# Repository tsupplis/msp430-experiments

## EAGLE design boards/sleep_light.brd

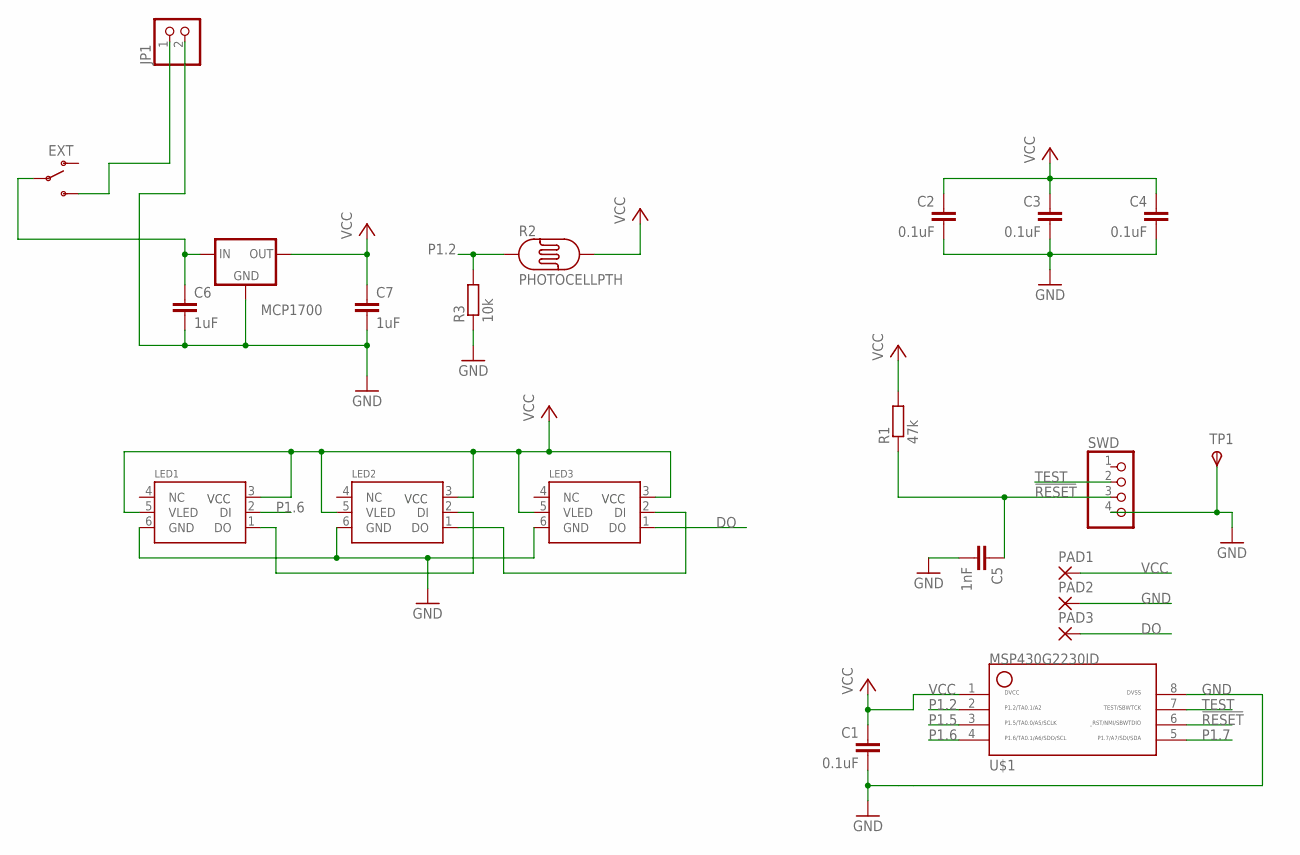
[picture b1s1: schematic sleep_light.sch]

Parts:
C1, C2, C3, C4: 0.1uF; C0805
C5: 1nF; C0805
C6, C7: 1uF; C0805
JP1: PINHD-1X2; 1X02
LED1, LED2, LED3: 5050WS2811W; RGBLED5050W
MCP1700: MCP1700; SOT-23
ON: EXT; SWITCH-SPDT
PAD1, PAD2, PAD3: SMD2; SMD1,27-2,54
R1: 47k; R0805
R2: PHOTOCELLPTH; PHOTOCELL
R3: 10k; R0805
SWD: PINHD-1X4; 1X04
TP1: TPSTP20R; TP20R
U$1: MSP430G2230ID; SO08

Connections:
!RESET: C5.1, R1.1, SWD.3, U$1.6
DO: LED3.1 (DO), PAD3.1
GND: C1.2, C2.2, C3.2, C4.2, C5.2, C6.2, C7.2, JP1.2, LED1.6 (GND), LED2.6 (GND), LED3.6 (GND), MCP1700.1 (GND), PAD2.1, R3.1, SWD.4, TP1.TP, U$1.8
unnamed: JP1.1, ON.3 (S)
unnamed: LED2.1 (DO), LED3.2 (DI)
unnamed: LED1.1 (DO), LED2.2 (DI)
unnamed: C6.1, MCP1700.3 (IN), ON.2
P1.2: R2.1, R3.2, U$1.2
P1.5: U$1.3
P1.6: LED1.2 (DI), U$1.4
P1.7: U$1.5
TEST: SWD.2, U$1.7
VCC: C1.1, C2.1, C3.1, C4.1, C7.1, LED1.3 (VCC), LED1.5 (VLED), LED2.3 (VCC), LED2.5 (VLED), LED3.3 (VCC), LED3.5 (VLED), MCP1700.2 (OUT), PAD1.1, R1.2, R2.2, U$1.1

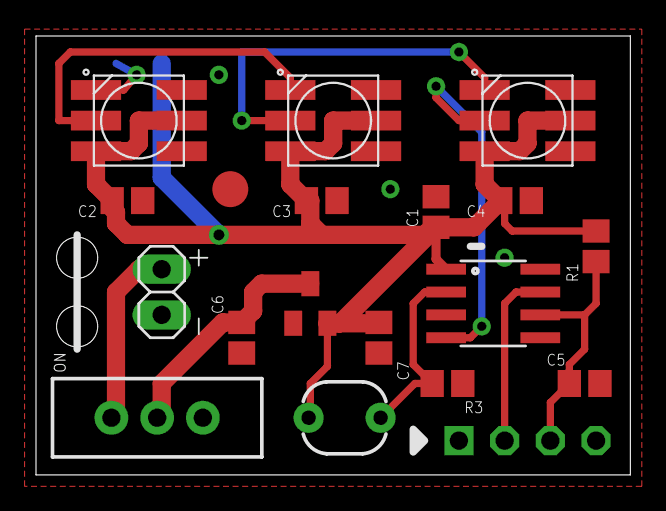
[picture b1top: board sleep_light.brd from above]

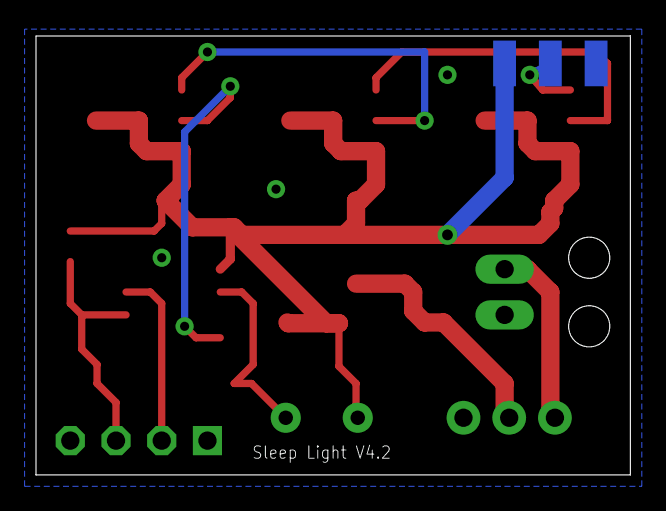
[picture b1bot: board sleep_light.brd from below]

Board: 2 copper layers, 33.0 x 24.4 mm, 22 parts (3 on the bottom side), 11 nets.

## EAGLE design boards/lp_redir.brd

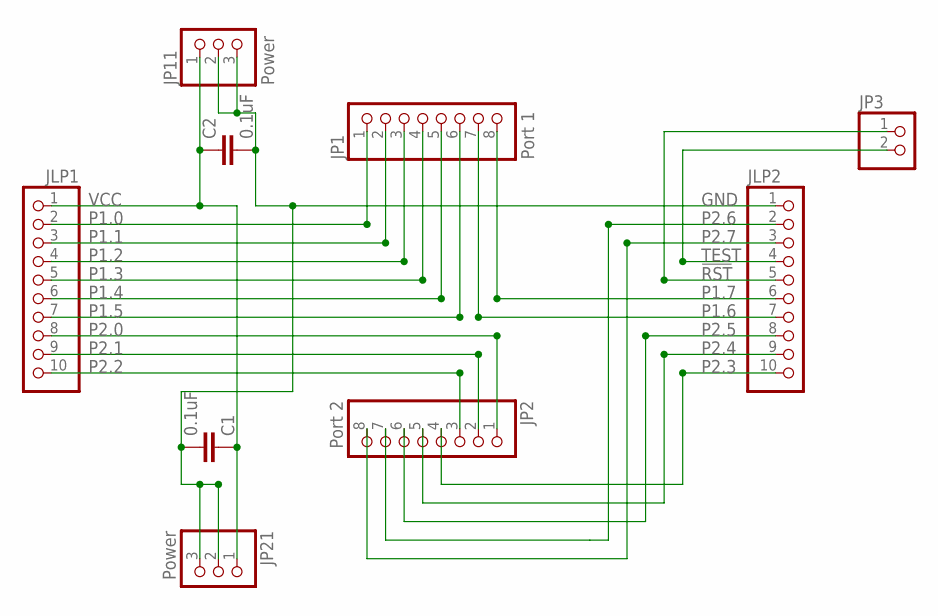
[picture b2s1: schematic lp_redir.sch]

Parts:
C1, C2: 0.1uF; C025-025X050
JLP1, JLP2: PH1X10OCT076; PH1X10OCT76
JP1: Port 1; 1X08
JP2: Port 2; 1X08
JP3: 1X02
JP11, JP21: Power; 1X03

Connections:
!RST: JLP2.5, JP3.1
GND: C1.2, C2.2, JLP2.1, JP11.2, JP11.3, JP21.2, JP21.3
P1.0: JLP1.2, JP1.1
P1.1: JLP1.3, JP1.2
P1.2: JLP1.4, JP1.3
P1.3: JLP1.5, JP1.4
P1.4: JLP1.6, JP1.5
P1.5: JLP1.7, JP1.6
P1.6: JLP2.7, JP1.7
P1.7: JLP2.6, JP1.8
P2.0: JLP1.8, JP2.1
P2.1: JLP1.9, JP2.2
P2.2: JLP1.10, JP2.3
P2.3: JLP2.10, JP2.4
P2.4: JLP2.9, JP2.5
P2.5: JLP2.8, JP2.6
P2.6: JLP2.2, JP2.7
P2.7: JLP2.3, JP2.8
TEST: JLP2.4, JP3.2
VCC: C1.1, C2.1, JLP1.1, JP11.1, JP21.1

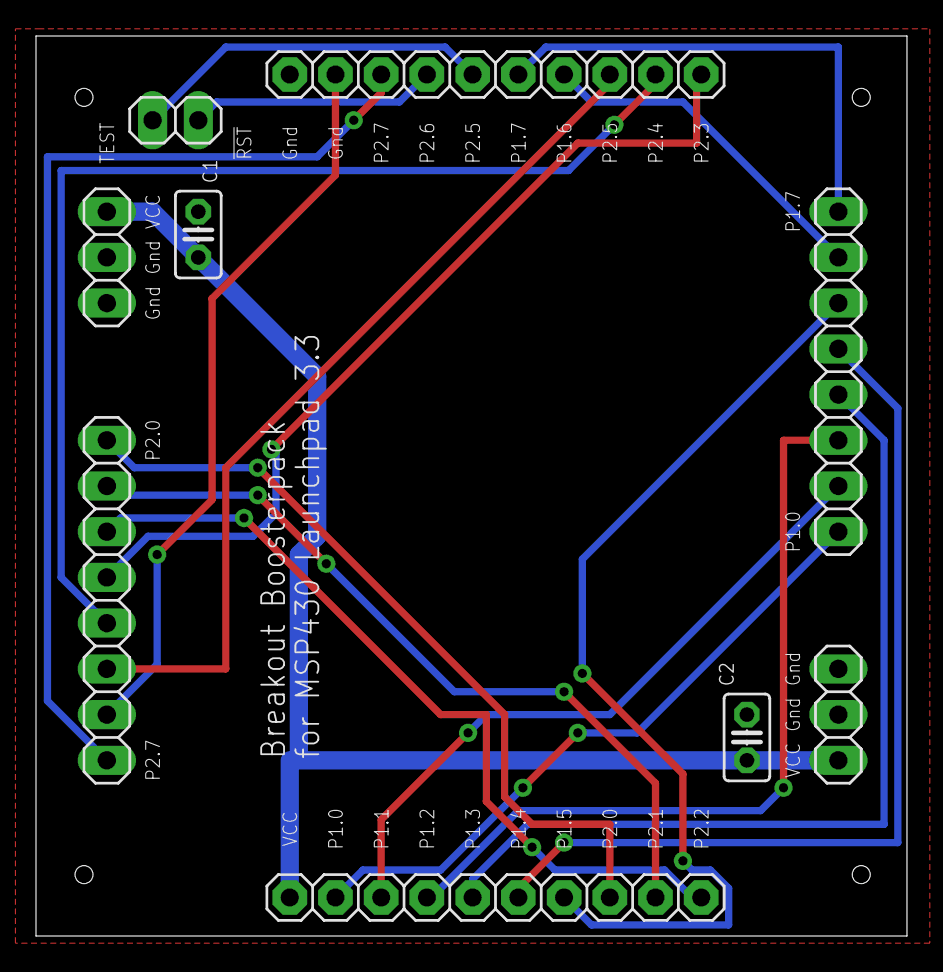
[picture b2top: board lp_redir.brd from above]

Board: 2 copper layers, 48.4 x 50.0 mm, 9 parts (0 on the bottom side), 20 nets.

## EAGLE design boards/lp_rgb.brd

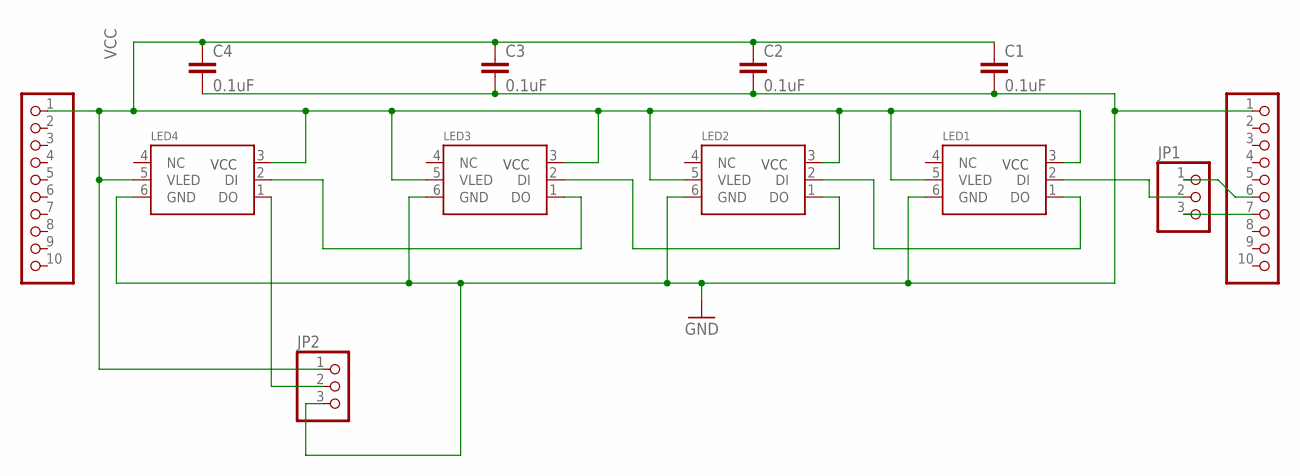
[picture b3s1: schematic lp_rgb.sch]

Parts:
C1, C2, C3, C4: 0.1uF; C0805
J1: J1; 1X10
J2: J2; 1X10
JP1, JP2: PINHD-1X3; 1X03
LED1, LED2, LED3, LED4: 5050WS2811W; RGBLED5050W

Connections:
GND: C1.2, C2.2, C3.2, C4.2, J2.1, JP2.3, LED1.6 (GND), LED2.6 (GND), LED3.6 (GND), LED4.6 (GND)
unnamed: J2.6, JP1.1
unnamed: JP2.2, LED4.1 (DO)
unnamed: LED1.1 (DO), LED2.2 (DI)
unnamed: LED2.1 (DO), LED3.2 (DI)
unnamed: LED3.1 (DO), LED4.2 (DI)
unnamed: J2.7, JP1.3
P1.6: JP1.2, LED1.2 (DI)
VCC: C1.1, C2.1, C3.1, C4.1, J1.1, JP2.1, LED1.3 (VCC), LED1.5 (VLED), LED2.3 (VCC), LED2.5 (VLED), LED3.3 (VCC), LED3.5 (VLED), LED4.3 (VCC), LED4.5 (VLED)

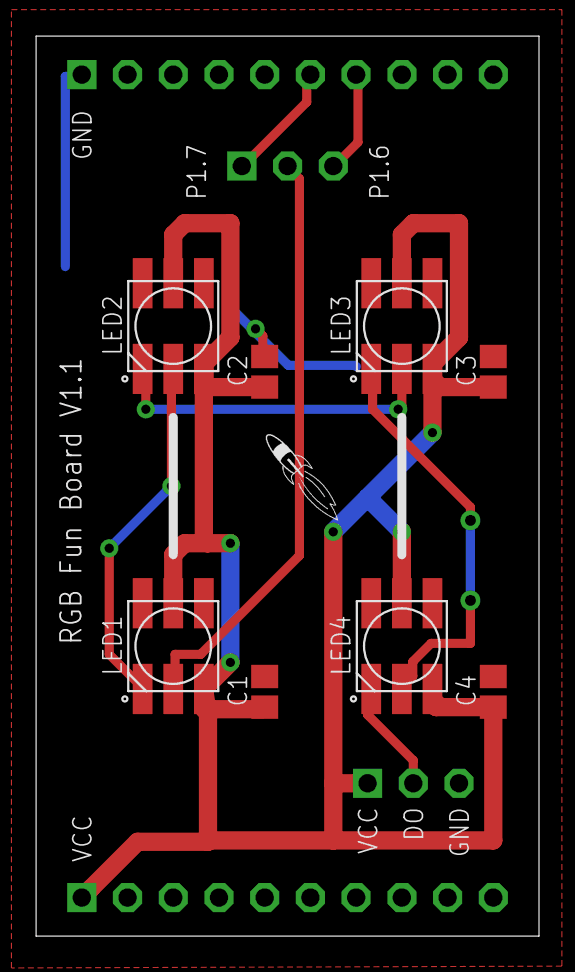
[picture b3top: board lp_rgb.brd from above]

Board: 2 copper layers, 27.9 x 50.0 mm, 13 parts (0 on the bottom side), 9 nets.

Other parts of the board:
U$2: LOGO-ROCKET

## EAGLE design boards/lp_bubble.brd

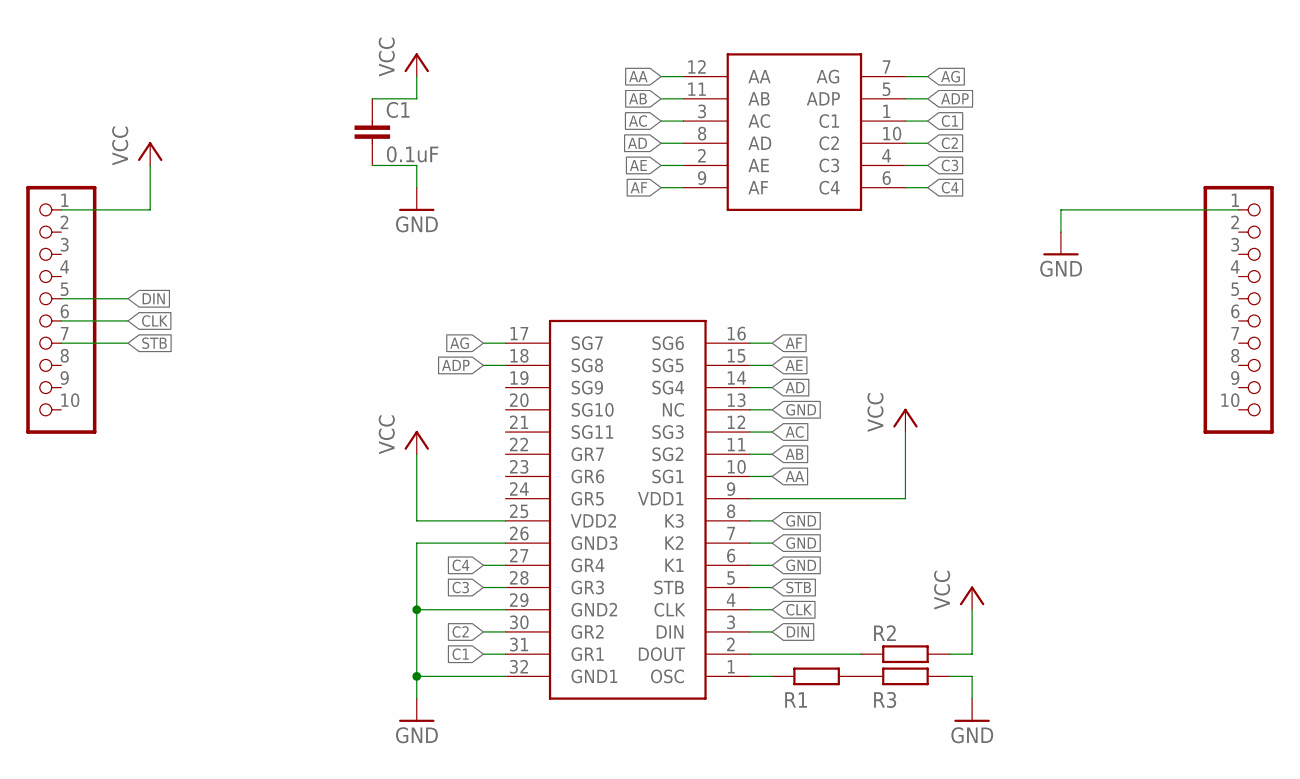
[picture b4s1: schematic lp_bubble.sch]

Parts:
C1: 0.1uF; C0805
J1: J1; 1X10
J2: J2; 1X10
R1: 50K; M0805
R2: 10K; M0805
R3: 1K; M0805
U$1: HP5082-7414
U$3: PT6961

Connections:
AA: U$1.12 (AA), U$3.10 (SG1)
AB: U$1.11 (AB), U$3.11 (SG2)
AC: U$1.3 (AC), U$3.12 (SG3)
AD: U$1.8 (AD), U$3.14 (SG4)
ADP: U$1.5 (ADP), U$3.18 (SG8)
AE: U$1.2 (AE), U$3.15 (SG5)
AF: U$1.9 (AF), U$3.16 (SG6)
AG: U$1.7 (AG), U$3.17 (SG7)
C1: U$1.1 (C1), U$3.31 (GR1)
C2: U$1.10 (C2), U$3.30 (GR2)
C3: U$1.4 (C3), U$3.28 (GR3)
C4: U$1.6 (C4), U$3.27 (GR4)
CLK: J1.6, U$3.4 (CLK)
DIN: J1.5, U$3.3 (DIN)
GND: C1.2, J2.1, R3.2, U$3.6 (K1), U$3.7 (K2), U$3.8 (K3), U$3.13 (NC), U$3.26 (GND3), U$3.29 (GND2), U$3.32 (GND1)
unnamed: R1.2, R3.1
unnamed: R1.1, U$3.1 (OSC)
unnamed: R2.1, U$3.2 (DOUT)
STB: J1.7, U$3.5 (STB)
VCC: C1.1, J1.1, R2.2, U$3.9 (VDD1), U$3.25 (VDD2)

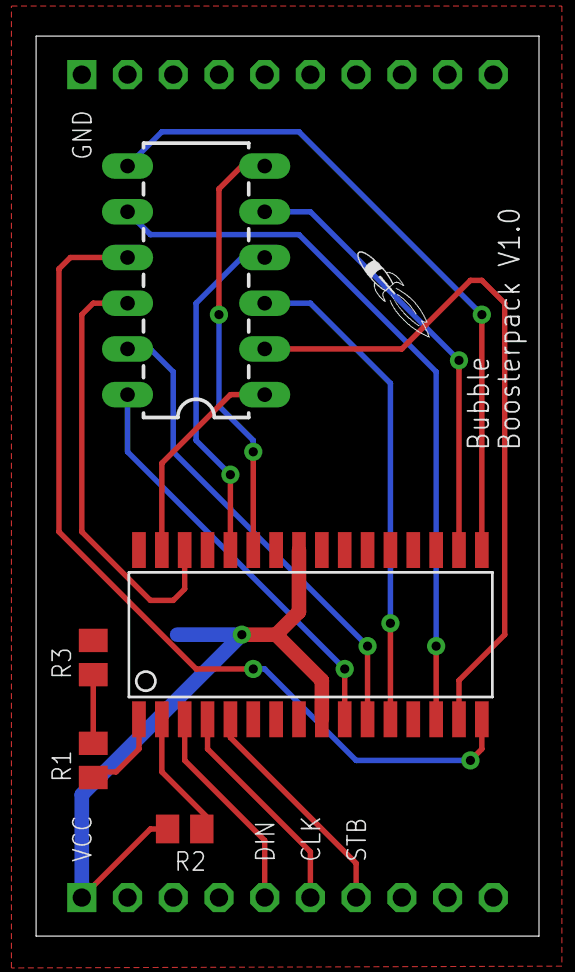
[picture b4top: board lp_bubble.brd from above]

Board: 2 copper layers, 27.9 x 50.0 mm, 9 parts (1 on the bottom side), 20 nets.

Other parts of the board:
U$2: LOGO-ROCKET

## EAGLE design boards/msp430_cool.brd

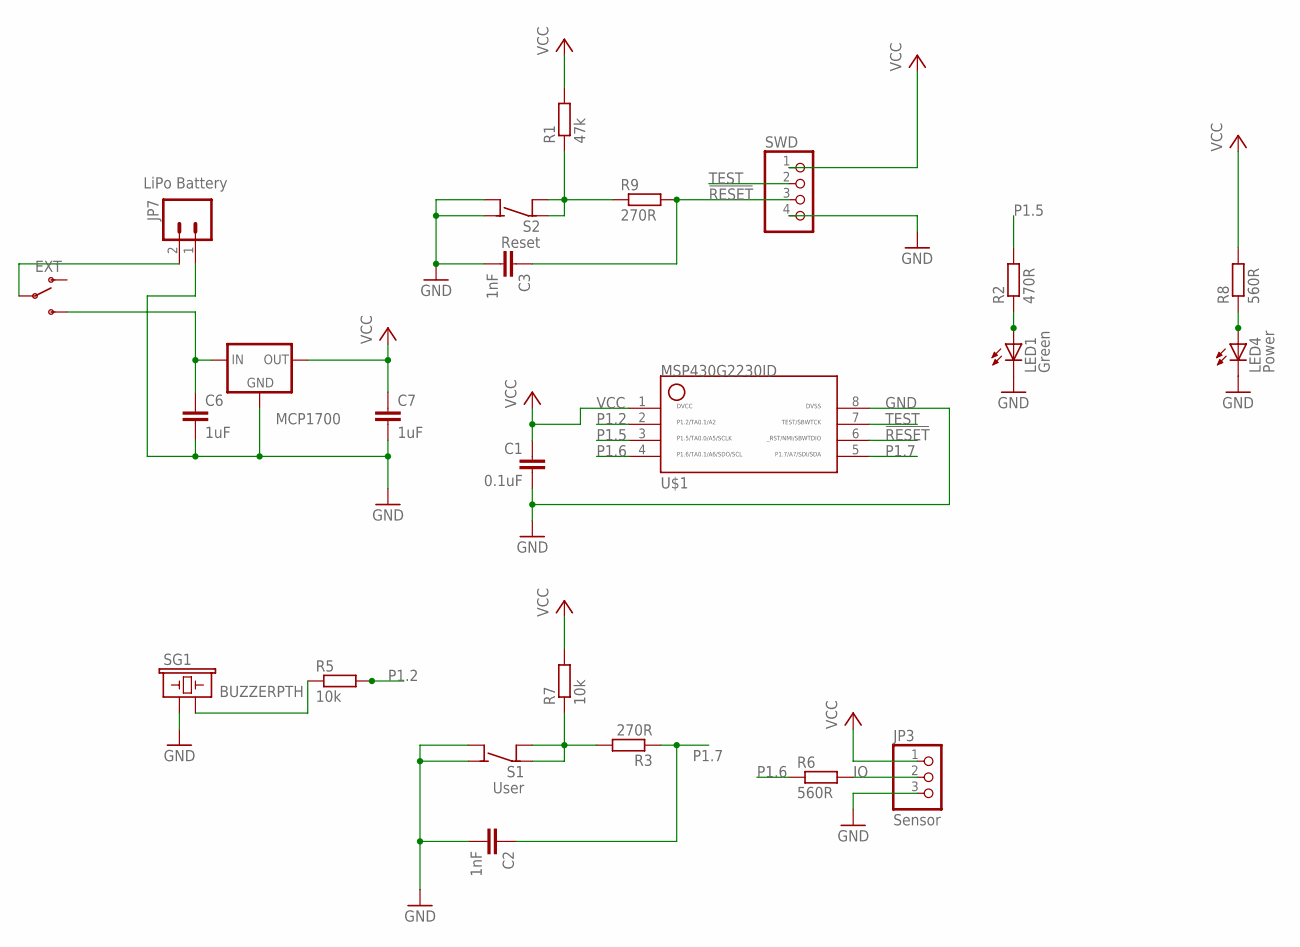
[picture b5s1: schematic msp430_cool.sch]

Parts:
C1: 0.1uF; C0805
C2, C3: 1nF; C0805
C6, C7: 1uF; C0805
JP3: Sensor; 1X03
JP7: LiPo Battery; JST-2-PTH
LED1: Green; CHIPLED_1206
LED4: Power; CHIPLED_1206
MCP1700: MCP1700; SOT-23
ON: EXT; SWITCH-SPDT
R1: 47k; R0805
R2: 470R; R0805
R3, R9: 270R; R0805
R5, R7: 10k; R0805
R6, R8: 560R; R0805
S1: User; 6MMTACTILE_4PIN
S2: Reset; 6MMTACTILE_4PIN
SG1: BUZZERPTH; BUZZER-12MM
SWD: PINHD-1X4; 1X04
U$1: MSP430G2230ID; SO08

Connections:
!RESET: C3.1, R9.2, SWD.3, U$1.6
GND: C1.2, C2.2, C3.2, C6.2, C7.2, JP3.3, JP7.1, LED1.C, LED4.C, MCP1700.1 (GND), S1.A1 (NO), S1.A2 (NO), S2.A1 (NO), S2.A2 (NO), SG1.+ (1), SWD.4, U$1.8
IO: JP3.2, R6.2
unnamed: LED4.A, R8.1
unnamed: JP7.2, ON.2
unnamed: LED1.A, R2.1
unnamed: R1.1, R9.1, S2.B1 (COM), S2.B2 (COM)
unnamed: R5.1, SG1.- (2)
unnamed: R3.2, R7.1, S1.B1 (COM), S1.B2 (COM)
unnamed: C6.1, MCP1700.3 (IN), ON.3 (S)
P1.2: R5.2, U$1.2
P1.5: R2.2, U$1.3
P1.6: R6.1, U$1.4
P1.7: C2.1, R3.1, U$1.5
TEST: SWD.2, U$1.7
VCC: C1.1, C7.1, JP3.1, MCP1700.2 (OUT), R1.2, R7.2, R8.2, SWD.1, U$1.1

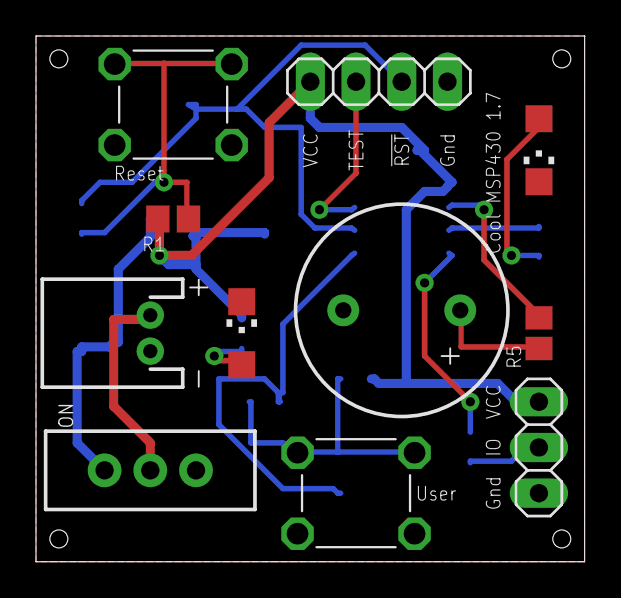
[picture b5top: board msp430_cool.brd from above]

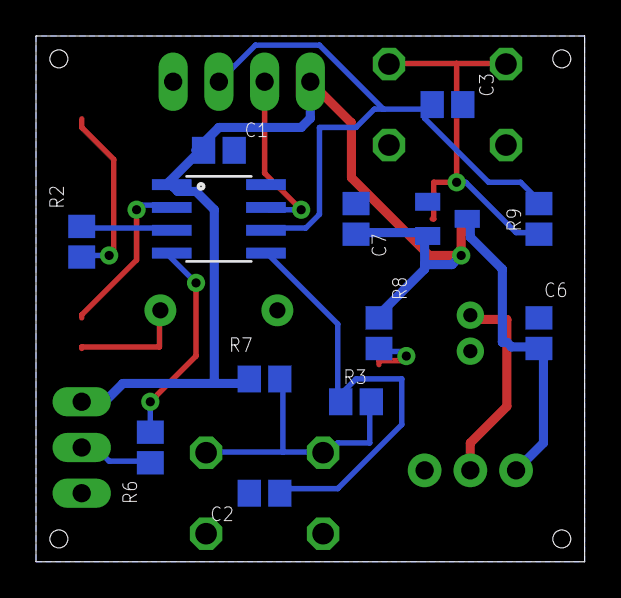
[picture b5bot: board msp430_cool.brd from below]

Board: 2 copper layers, 30.5 x 29.2 mm, 24 parts (13 on the bottom side), 16 nets.

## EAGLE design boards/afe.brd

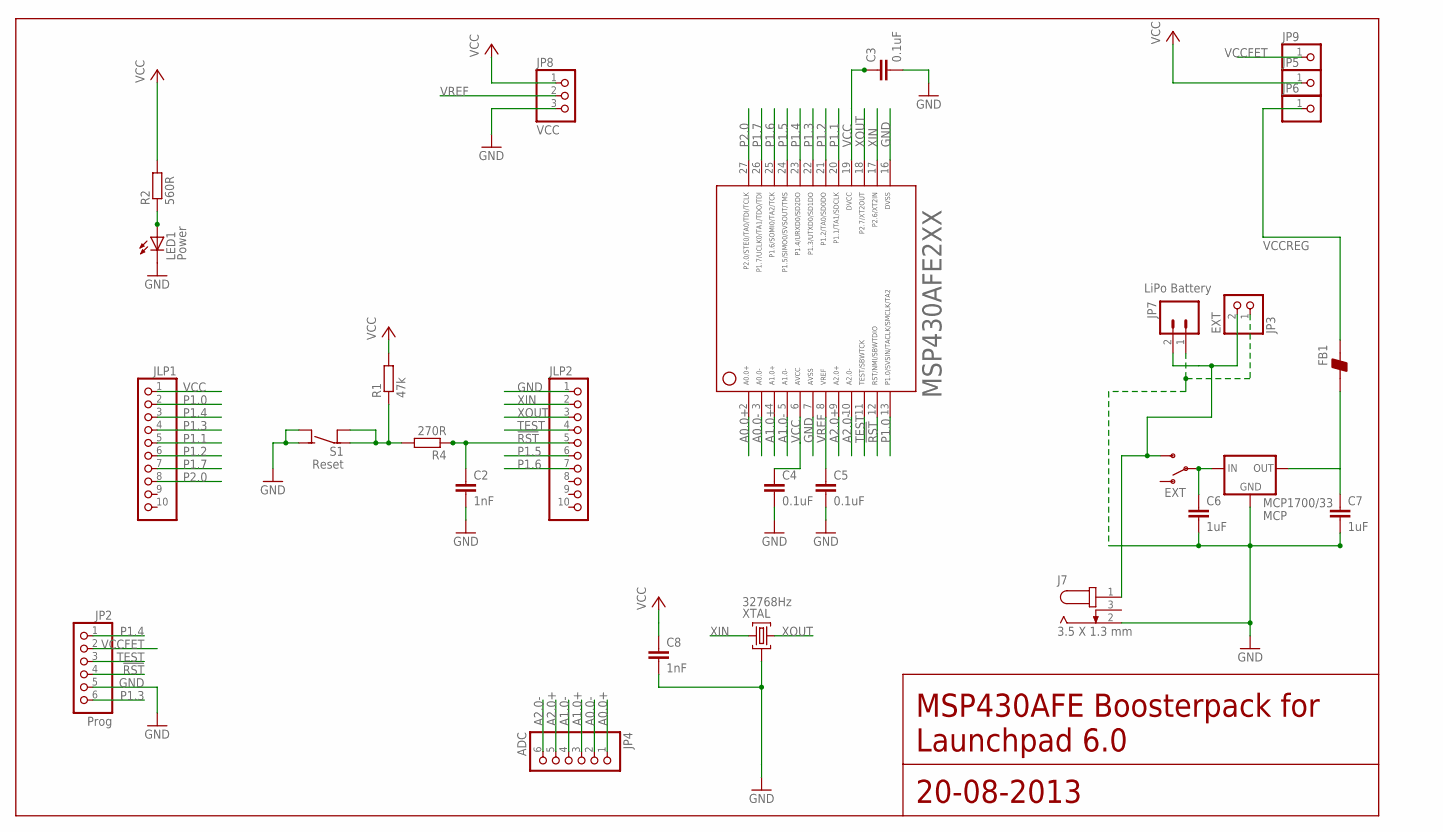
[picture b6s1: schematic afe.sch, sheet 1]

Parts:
C2, C8: 1nF; C0805
C3, C4, C5: 0.1uF; C0805
C6, C7: 1uF; C0805
FB1: BEAD-0805; 0805
J7: 3.5 X 1.3 mm; 3.5X1.3MM_DC_JACK
JLP1, JLP2: PH1X10OCT076; PH1X10OCT76
JP2: Prog; 1X06
JP3: EXT; 1X02
JP4: ADC; 1X06
JP5, JP6, JP9: PINHD-1X1; 1X01
JP7: LiPo Battery; JST-2-PTH
JP8: VCC; 1X03
LED1: Power; CHIPLED_1206
MCP1700/33: MCP; SOT-23
MSP430AFE: AFE2XX--PW24; PW24
ON: EXT; SWITCH-SPDT
R1: 47k; R0805
R2: 560R; R0805
R4: 270R; R0805
S1: Reset; 6MMTACTILE_4PIN
XTAL: 32768Hz; QUARZ5

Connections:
!RST: C2.1, JLP2.5, JP2.4, MSP430AFE.12 (11), R4.1
A0.0+: JP4.1, MSP430AFE.2 (1)
A0.0-: JP4.2, MSP430AFE.3 (2)
A1.0+: JP4.3, MSP430AFE.4 (3)
A1.0-: JP4.4, MSP430AFE.5 (4)
A2.0+: JP4.5, MSP430AFE.9 (8)
A2.0-: JP4.6, MSP430AFE.10 (9)
GND: C2.2, C3.2, C4.2, C5.2, C6.2, C7.2, C8.2, J7.2, JLP2.1, JP2.5, JP3.1, JP7.1, JP8.3, LED1.C, MCP1700/33.1 (GND), MSP430AFE.7 (6), MSP430AFE.16 (13), S1.A1 (NO), S1.A2 (NO), XTAL.GND@0 (0)
unnamed: LED1.A, R2.1
unnamed: R1.1, R4.2, S1.B1 (COM), S1.B2 (COM)
P1.0: JLP1.2, MSP430AFE.13 (12)
P1.1: JLP1.5, MSP430AFE.20 (17)
P1.2: JLP1.6, MSP430AFE.21 (18)
P1.3: JLP1.4, JP2.6, MSP430AFE.22 (19)
P1.4: JLP1.3, JP2.1, MSP430AFE.23 (20)
P1.5: JLP2.6, MSP430AFE.24 (21)
P1.6: JLP2.7, MSP430AFE.25 (22)
P1.7: JLP1.7, MSP430AFE.26 (23)
P2.0: JLP1.8, MSP430AFE.27 (24)
TEST: JLP2.4, JP2.3, MSP430AFE.11 (10)
VCC: C3.1, C4.1, C8.1, JLP1.1, JP5.1, JP8.1, MSP430AFE.6 (5), MSP430AFE.19 (16), R1.2, R2.2
VCCEXT: J7.1, JP3.2, JP7.2, ON.3 (S)
VCCFET: JP2.2, JP9.1
VCCIN: C6.1, MCP1700/33.3 (IN), ON.2
VCCREG: FB1.2, JP6.1
VCCREGOUT: C7.1, FB1.1, MCP1700/33.2 (OUT)
VREF: C5.1, JP8.2, MSP430AFE.8 (7)
XIN: JLP2.2, MSP430AFE.17 (14), XTAL.2
XOUT: JLP2.3, MSP430AFE.18 (15), XTAL.1

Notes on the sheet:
MSP430AFE Boosterpack for Launchpad 6.0
20-08-2013

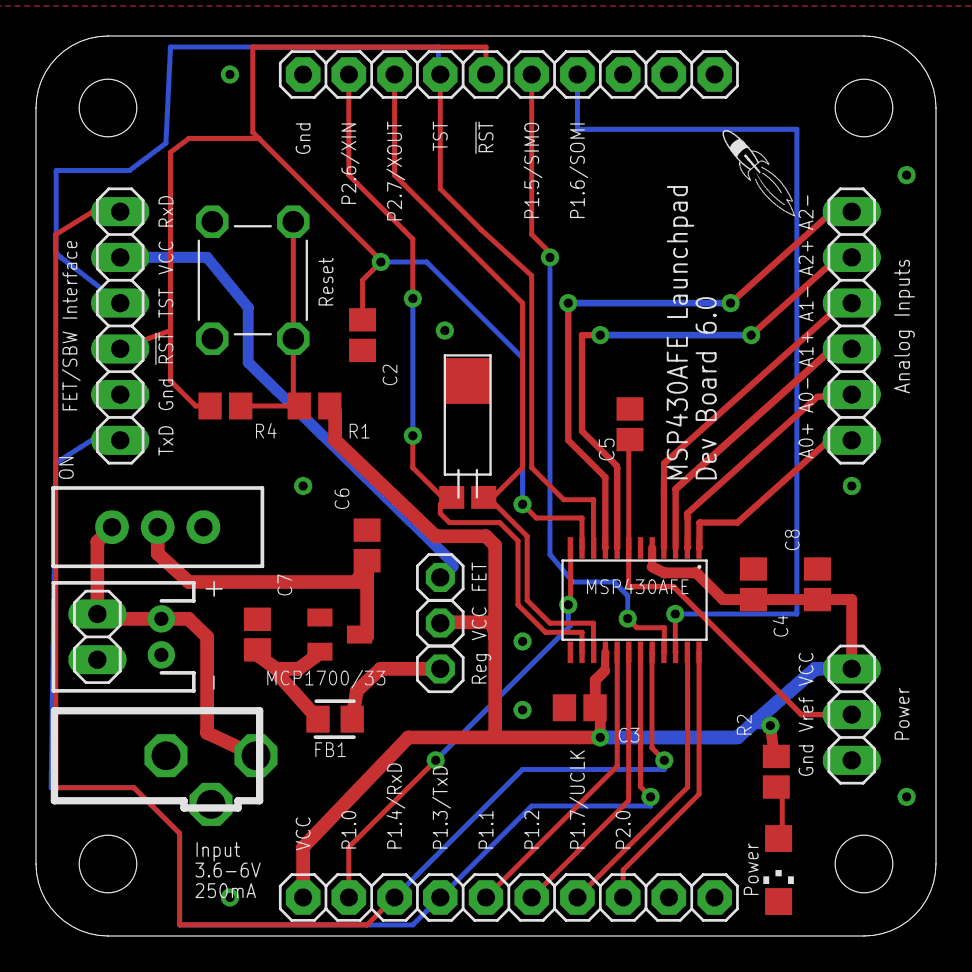
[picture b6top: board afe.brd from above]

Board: 2 copper layers, 50.0 x 50.0 mm, 30 parts (0 on the bottom side), 29 nets.

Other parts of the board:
U$1: DP5050_V1
U$2: LOGO-ROCKET

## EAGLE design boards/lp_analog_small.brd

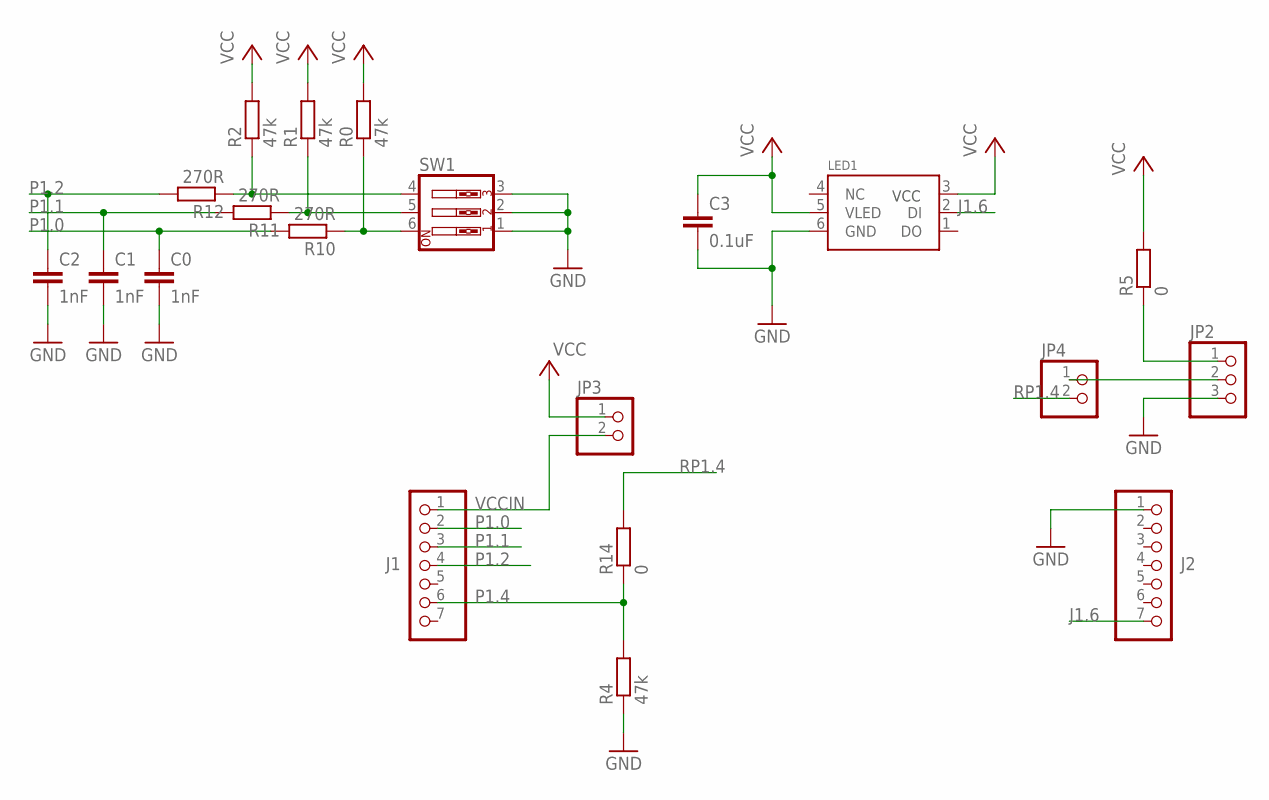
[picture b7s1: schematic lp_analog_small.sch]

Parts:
C0, C1, C2: 1nF; C0805
C3: 0.1uF; C0805
J1, J2: PINHD-1X7; 1X07
JP2: PINHD-1X3; 1X03
JP3, JP4: PINHD-1X2; 1X02
LED1: 5050WS2811W; RGBLED5050W
R0, R1, R2, R4: 47k; R0805
R5, R14: 0; R0805
R10, R11, R12: 270R; R0805
SW1: SW_DIP-3; EDG-03

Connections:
GND: C0.2, C1.2, C2.2, C3.2, J2.1, JP2.3, LED1.6 (GND), R4.1, SW1.1, SW1.2, SW1.3
J1.6: J2.7, LED1.2 (DI)
unnamed: R2.1, R12.1, SW1.4
unnamed: R1.1, R11.1, SW1.5
unnamed: JP2.2, JP4.1
unnamed: JP2.1, R5.1
unnamed: R0.1, R10.1, SW1.6
P1.0: C0.1, J1.2, R10.2
P1.1: C1.1, J1.3, R11.2
P1.2: C2.1, J1.4, R12.2
P1.4: J1.6, R4.2, R14.1
RP1.4: JP4.2, R14.2
VCC: C3.1, JP3.1, LED1.3 (VCC), LED1.5 (VLED), R0.2, R1.2, R2.2, R5.2
VCCIN: J1.1, JP3.2

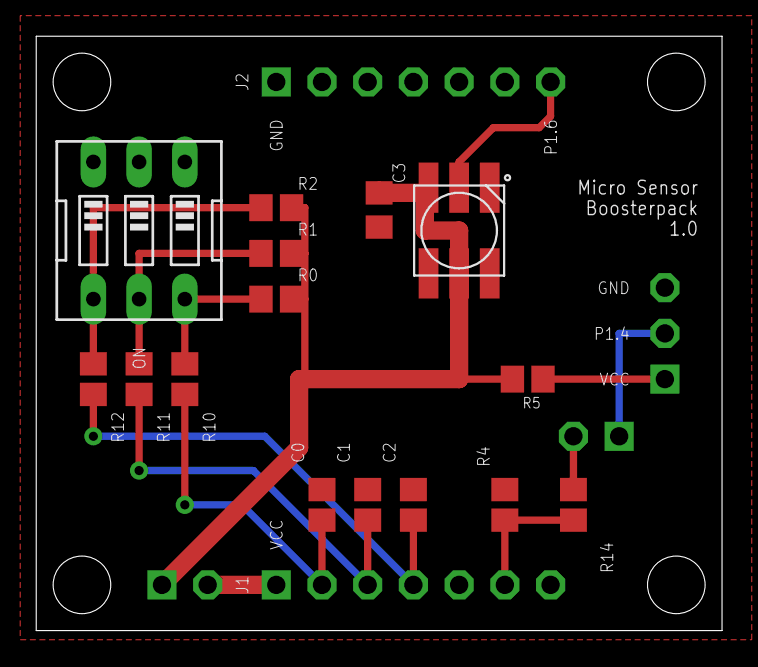
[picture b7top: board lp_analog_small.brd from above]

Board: 2 copper layers, 38.1 x 33.0 mm, 20 parts (0 on the bottom side), 14 nets.

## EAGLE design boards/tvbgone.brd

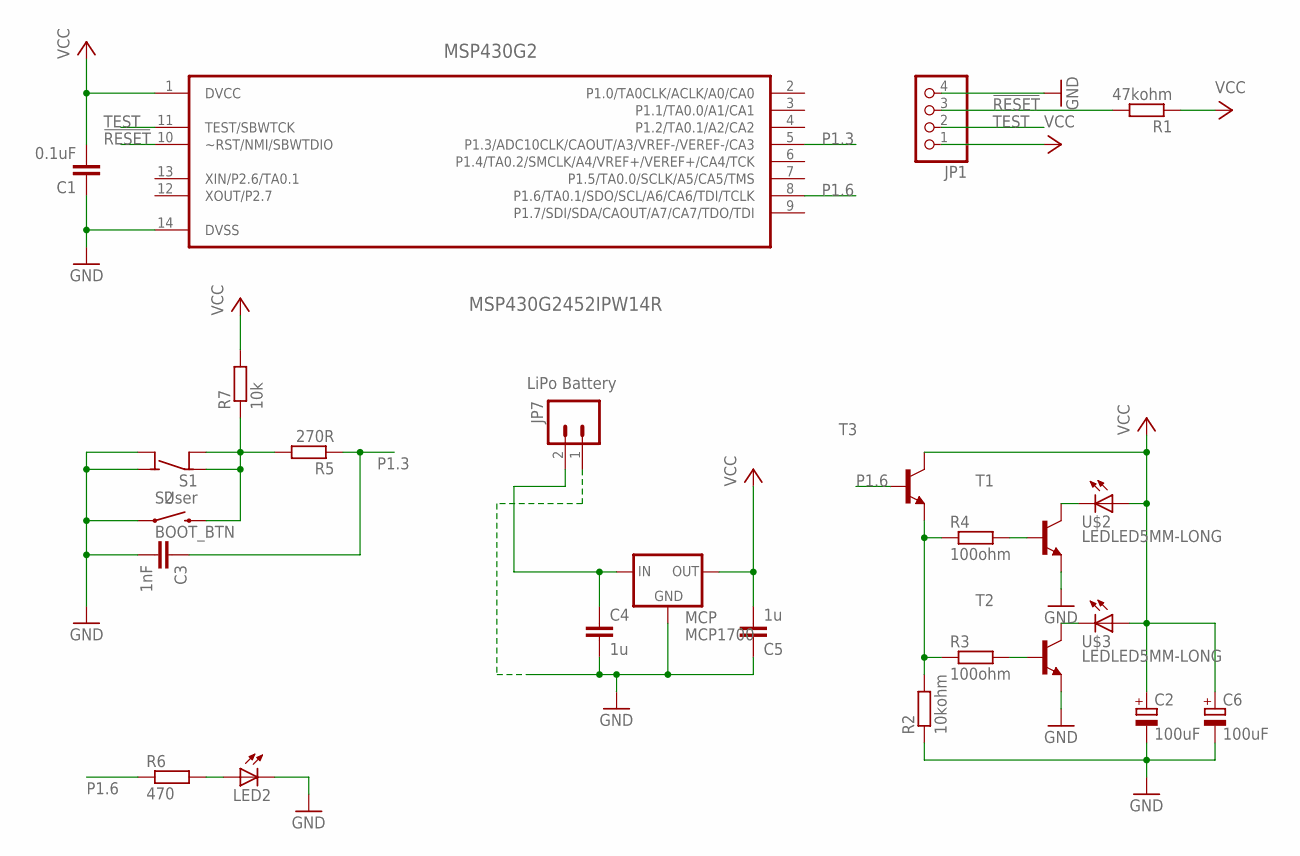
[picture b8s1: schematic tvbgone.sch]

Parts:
C1: 0.1uF; C0805
C2: 100uF; 153CLV-0505
C3: 1nF; C0805
C4, C5: 1u; C0805
C6: 100uF; E3,5-8
JP1: PINHD-1X4; 1X04
JP7: LiPo Battery; JST-2-PTH
LED2: 0; CHIPLED_1206
MCP: MCP1700; SOT-23
MSP430G2: MSP430G2452IPW14R; SOP65P640X120-14N
R1: 47kohm; R0805
R2: 10kohm; R0805
R3, R4: 100ohm; R0805
R5: 270R; R0805
R6: 470; R0805
R7: 10k; R0805
S1: User; 6MMTACTILE_4PIN
S2: BOOT_BTN; TACTILE-SWITCH-1101NE
T1, T2, T3: MMBT2222ALT1-NPN-SOT23-BEC; SOT23-BEC
U$2, U$3: LEDLED5MM-LONG; LED5MM-LONG

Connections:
!RESET: JP1.3, MSP430G2.10 (~RST/NMI/SBWTDIO), R1.2
GND: C1.1, C2.-, C3.2, C4.2, C5.1, C6.-, JP1.4, JP7.1, LED2.C, MCP.1 (GND), MSP430G2.14 (DVSS), R2.1, S1.A1 (NO), S1.A2 (NO), S2.1, T1.E, T2.E
unnamed: R5.2, R7.1, S1.B1 (COM), S1.B2 (COM), S2.2
unnamed: R2.2, R3.1, R4.1, T3.E
unnamed: T2.C, U$3.C
unnamed: T1.C, U$2.C
unnamed: R4.2, T1.B
unnamed: R3.2, T2.B
unnamed: LED2.A, R6.2
P1.3: C3.1, MSP430G2.5 (P1.3/ADC10CLK/CAOUT/A3/VREF-/VEREF-/CA3), R5.1
P1.6: MSP430G2.8 (P1.6/TA0.1/SDO/SCL/A6/CA6/TDI/TCLK), R6.1, T3.B
TEST: JP1.2, MSP430G2.11 (TEST/SBWTCK)
VCC: C1.2, C2.+, C5.2, C6.+, JP1.1, MCP.2 (OUT), MSP430G2.1 (DVCC), R1.1, R7.2, T3.C, U$2.A, U$3.A
VCCEXT: C4.1, JP7.2, MCP.3 (IN)

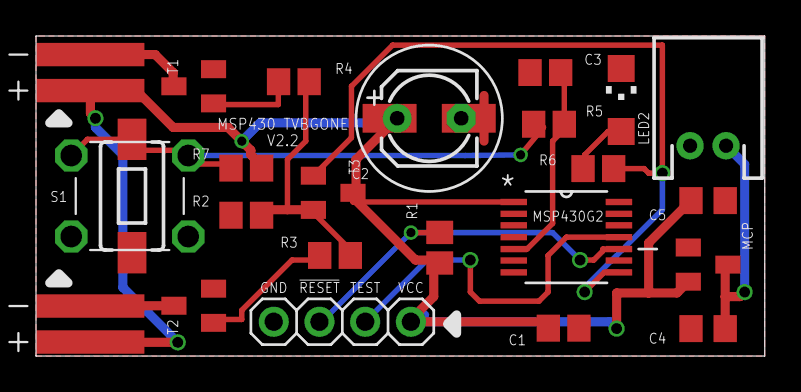
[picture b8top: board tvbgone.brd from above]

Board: 2 copper layers, 40.5 x 17.8 mm, 25 parts (0 on the bottom side), 14 nets.

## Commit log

2016-04-05 Initial Update
2016-04-05 Initial Content

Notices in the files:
parts and their libraries:
SparkFun: Licensing: CC v3.0 Share-Alike You are welcome to use this library for commercial purposes.
SparkFun-Electromechanical: Licensing: Creative Commons ShareAlike 4.0 International - https://creativecommons.org/licenses/by-sa/4.0
